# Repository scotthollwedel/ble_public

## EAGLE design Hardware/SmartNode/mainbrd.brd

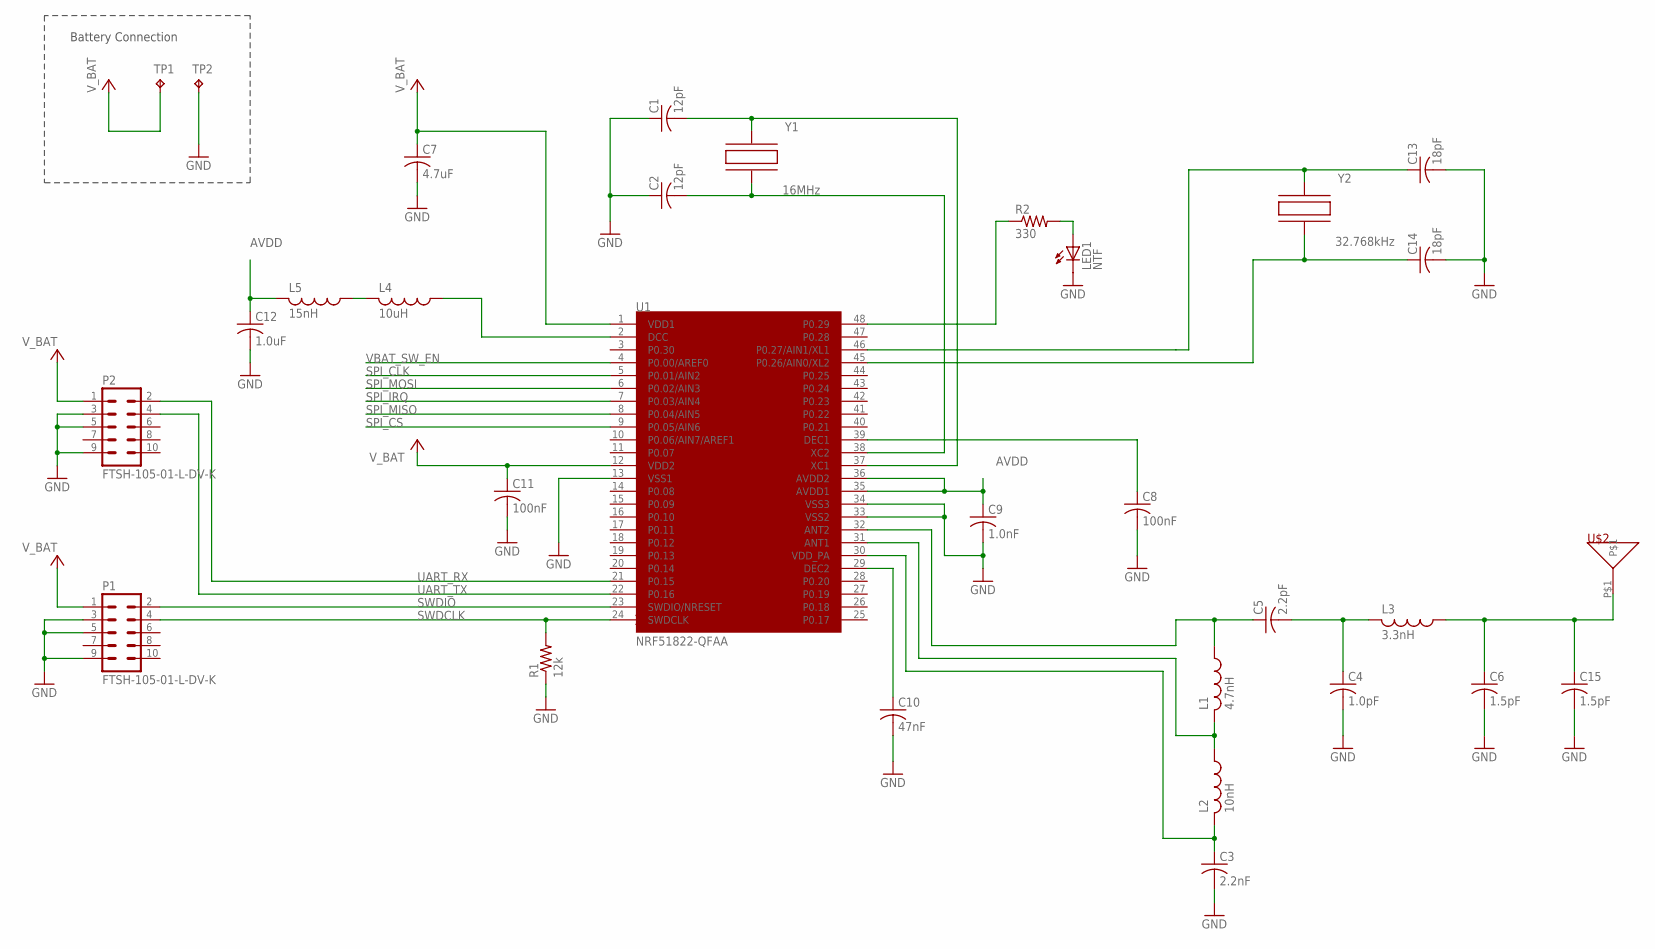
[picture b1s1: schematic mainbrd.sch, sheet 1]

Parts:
C1, C2: 12pF; C0402
C3: 2.2nF; C0402
C4: 1.0pF; C0402
C5: 2.2pF; C0402
C6, C15: 1.5pF; C0402
C7: 4.7uF; C0603
C8, C11: 100nF; C0402
C9: 1.0nF; C0402
C10: 47nF; C0402
C12: 1.0uF; C0603
C13, C14: 18pF; C0402
L1: 4.7nH; L0402
L2: 10nH; L0402
L3: 3.3nH; L0402
L4: 10uH; L0603
L5: 15nH; L0402
LED1: NTF; CHIP-LED0603
P1, P2: FTSH-105-01-L-DV-K
R1: 12k; R0402
R2: 330; R0402
TP1, TP2: TPPAD1-13; P1-13
U1: NRF51822-QFAA; QFN48
U$2: PCB_ANT
Y1: 16MHz; SMD_3225
Y2: 32.768kHz; ECX-39

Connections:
ANT: C6.1, C15.1, L3.1, U$2.P$1
AVDD: C9.1, C12.1, L5.2, U1.35 (AVDD1), U1.36 (AVDD2)
GND: C1.1, C2.1, C3.2, C4.2, C6.2, C7.2, C8.2, C9.2, C10.2, C11.2, C12.2, C13.2, C14.2, C15.2, LED1.C, P1.3, P1.5, P1.9, P2.3, P2.5, P2.9, R1.1, TP2.TP, U1.13 (VSS1), U1.33 (VSS2), U1.34 (VSS3); also elsewhere on the board
unnamed: L4.1, U1.2 (DCC)
unnamed: L4.2, L5.1
unnamed: C1.2, U1.37 (XC1), Y1.3
unnamed: C2.2, U1.38 (XC2), Y1.1
unnamed: C8.1, U1.39 (DEC1)
unnamed: C5.1, L1.1, U1.32 (ANT2)
unnamed: L1.2, L2.1, U1.31 (ANT1)
unnamed: C3.1, L2.2, U1.30 (VDD_PA)
unnamed: C10.1, U1.29 (DEC2)
unnamed: C4.1, C5.2, L3.2
unnamed: C13.1, U1.46 (P0.27/AIN1/XL1), Y2.2
unnamed: C14.1, U1.45 (P0.26/AIN0/XL2), Y2.1
unnamed: R2.1, U1.48 (P0.29)
unnamed: LED1.A, R2.2
SPI_CLK: U1.5 (P0.01/AIN2); also elsewhere on the board
SPI_CS: U1.9 (P0.05/AIN6); also elsewhere on the board
SPI_IRQ: U1.7 (P0.03/AIN4); also elsewhere on the board
SPI_MISO: U1.8 (P0.04/AIN5); also elsewhere on the board
SPI_MOSI: U1.6 (P0.02/AIN3); also elsewhere on the board
SWDCLK: P1.4, R1.2, U1.24 (SWDCLK)
SWDIO: P1.2, U1.23 (SWDIO/NRESET)
UART_RX: P2.2, U1.21 (P0.15)
UART_TX: P2.4, U1.22 (P0.16)
VBAT_SW_EN: U1.4 (P0.00/AREF0); also elsewhere on the board
VCC: C7.1, C11.1, P1.1, P2.1, TP1.TP, U1.1 (VDD1), U1.12 (VDD2); also elsewhere on the board

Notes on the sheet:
Battery Connection

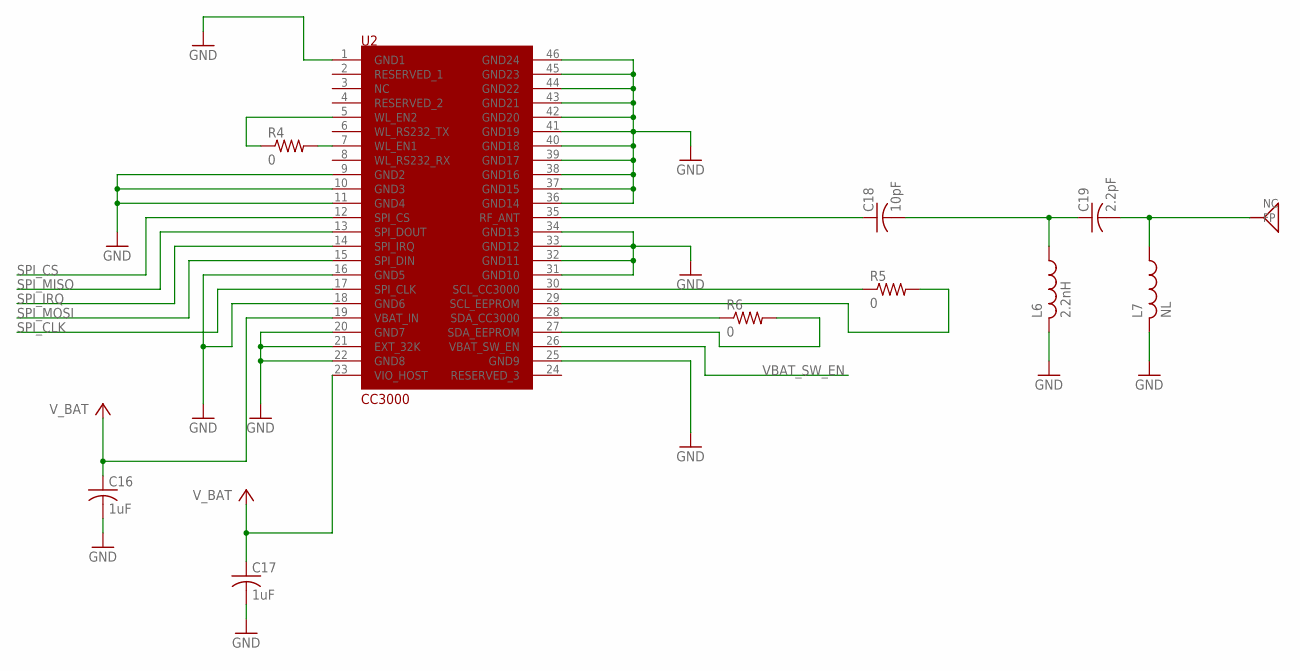
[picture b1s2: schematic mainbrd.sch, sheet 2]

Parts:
C16, C17: 1uF; C0402
C18: 10pF; C0402
C19: 2.2pF; C0402
L6: 2.2nH; L0402
L7: NL; L0402
R4, R5, R6: 0; R0402
U2: CC3000
U$1: AT8010

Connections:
GND: C16.2, C17.2, L6.2, L7.2, U2.1 (GND1), U2.9 (GND2), U2.10 (GND3), U2.11 (GND4), U2.16 (GND5), U2.18 (GND6), U2.20 (GND7), U2.21 (EXT_32K), U2.22 (GND8), U2.25 (GND9), U2.31 (GND10), U2.32 (GND11), U2.33 (GND12), U2.34 (GND13), U2.36 (GND14), U2.37 (GND15), U2.38 (GND16), U2.39 (GND17), U2.40 (GND18), U2.41 (GND19), U2.42 (GND20), U2.43 (GND21), U2.44 (GND22), U2.45 (GND23), U2.46 (GND24); also elsewhere on the board
unnamed: C19.2, L7.1, U$1.FP
unnamed: R4.1, U2.5 (WL_EN2)
unnamed: R4.2, U2.7 (WL_EN1)
unnamed: C18.2, C19.1, L6.1
unnamed: C18.1, U2.35 (RF_ANT)
unnamed: R5.2, U2.29 (SCL_EEPROM)
unnamed: R5.1, U2.30 (SCL_CC3000)
unnamed: R6.2, U2.27 (SDA_EEPROM)
unnamed: R6.1, U2.28 (SDA_CC3000)
SPI_CLK: U2.17 (SPI_CLK); also elsewhere on the board
SPI_CS: U2.12 (SPI_CS); also elsewhere on the board
SPI_IRQ: U2.14 (SPI_IRQ); also elsewhere on the board
SPI_MISO: U2.13 (SPI_DOUT); also elsewhere on the board
SPI_MOSI: U2.15 (SPI_DIN); also elsewhere on the board
VBAT_SW_EN: U2.26 (VBAT_SW_EN); also elsewhere on the board
VCC: C16.1, C17.1, U2.19 (VBAT_IN), U2.23 (VIO_HOST); also elsewhere on the board

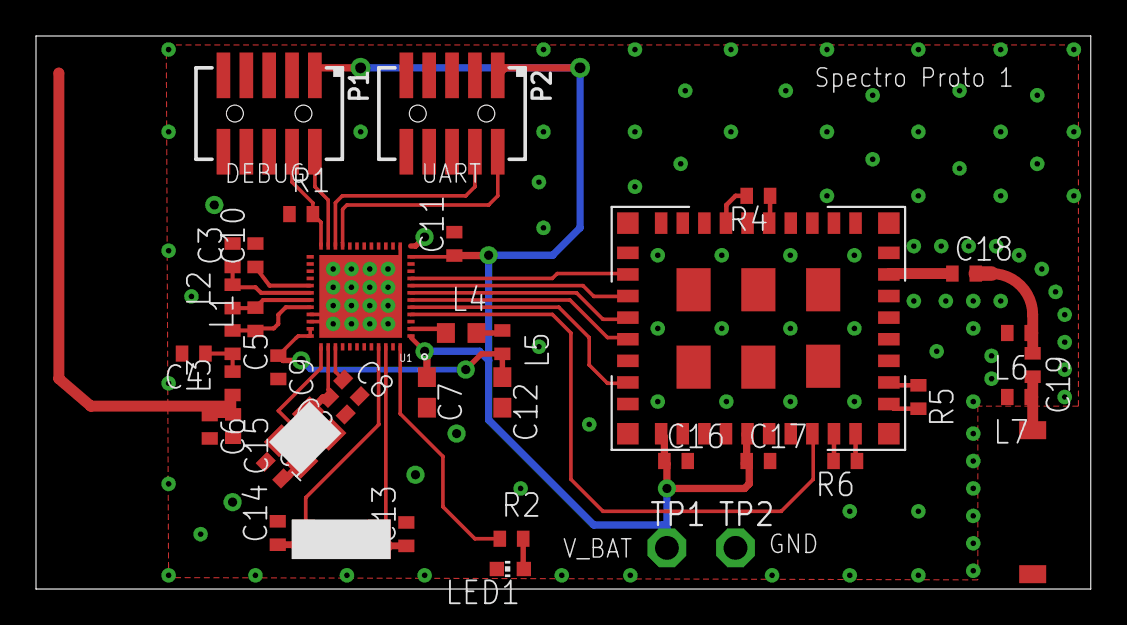
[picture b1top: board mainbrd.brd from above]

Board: 2 copper layers, 58.6 x 30.7 mm, 42 parts (0 on the bottom side), 37 nets.

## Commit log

2014-02-10 Add initial project
2014-02-10 Remove readme
2014-02-20 Add initial working version of BLE Beacon
2014-02-20 Remove original ibeacon code Add new project for customer transmitter project
2014-03-26 Add core functionality Add serial protocol
2014-04-29 Refactor code into seperate files
2014-04-29 Add one more file:wqa::
2014-05-04 Update to develop in linux
2014-05-04 Add new application to help with testing serial output
2014-05-04 Missed checkin
2014-05-04 make clean now removes JLink.log
2014-05-04 Add required headers and libraries for platform
2014-05-04 Change name to weyland
2014-05-04 Rename files
2014-05-04 Add support documents for project
2014-05-04 Add ability to flash via Makefile
2014-05-04 Fix problem with BLE TX Clean up some indentation issues
2014-05-07 Add spectro protocol sniffer Allow weyland to pilot correctly Add jlink deb
2014-05-19 Create seperate projects for all of the smart devices
2014-05-19 Add another new project for smart node
2014-05-19 Remove some errant commits Update smart_hub and smart_trans to use new serial protocol
2014-05-19 Add all changes for side projects so they at least compile
2014-06-15 Add hardware documents, schematics, and layout
2014-06-16 Updated Hardware Files
2014-08-20 Add project with Wifi driver
2014-08-20 catch up repos
2014-08-20 add root .gitignore file
2014-08-20 remove backup files
2014-08-20 sync everything up
2014-08-22 remove build files that should not be here
2014-08-22 Get basic HTTP working
2014-08-22 Remove a bunch of other build files
2014-08-28 Add JSON Parser jsmn Add basic JSON assembler Add ble and time files from old projects
2014-08-28 add version from git
2014-08-28 Trying new linker settings
2014-08-29 Add basic time calculator with 30 us resolution Add nonvolatile memory handling code
2014-08-30 Add battery voltage measurement code Split wifi code into seperate file Add push button backend sync
2014-08-30 Add adc and wifi files Add ability to send reports based on button press
2014-08-31 First largely working version of device API

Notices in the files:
parts and their libraries:
con-samtec: Copyright (C) 2009, Bob Starr
